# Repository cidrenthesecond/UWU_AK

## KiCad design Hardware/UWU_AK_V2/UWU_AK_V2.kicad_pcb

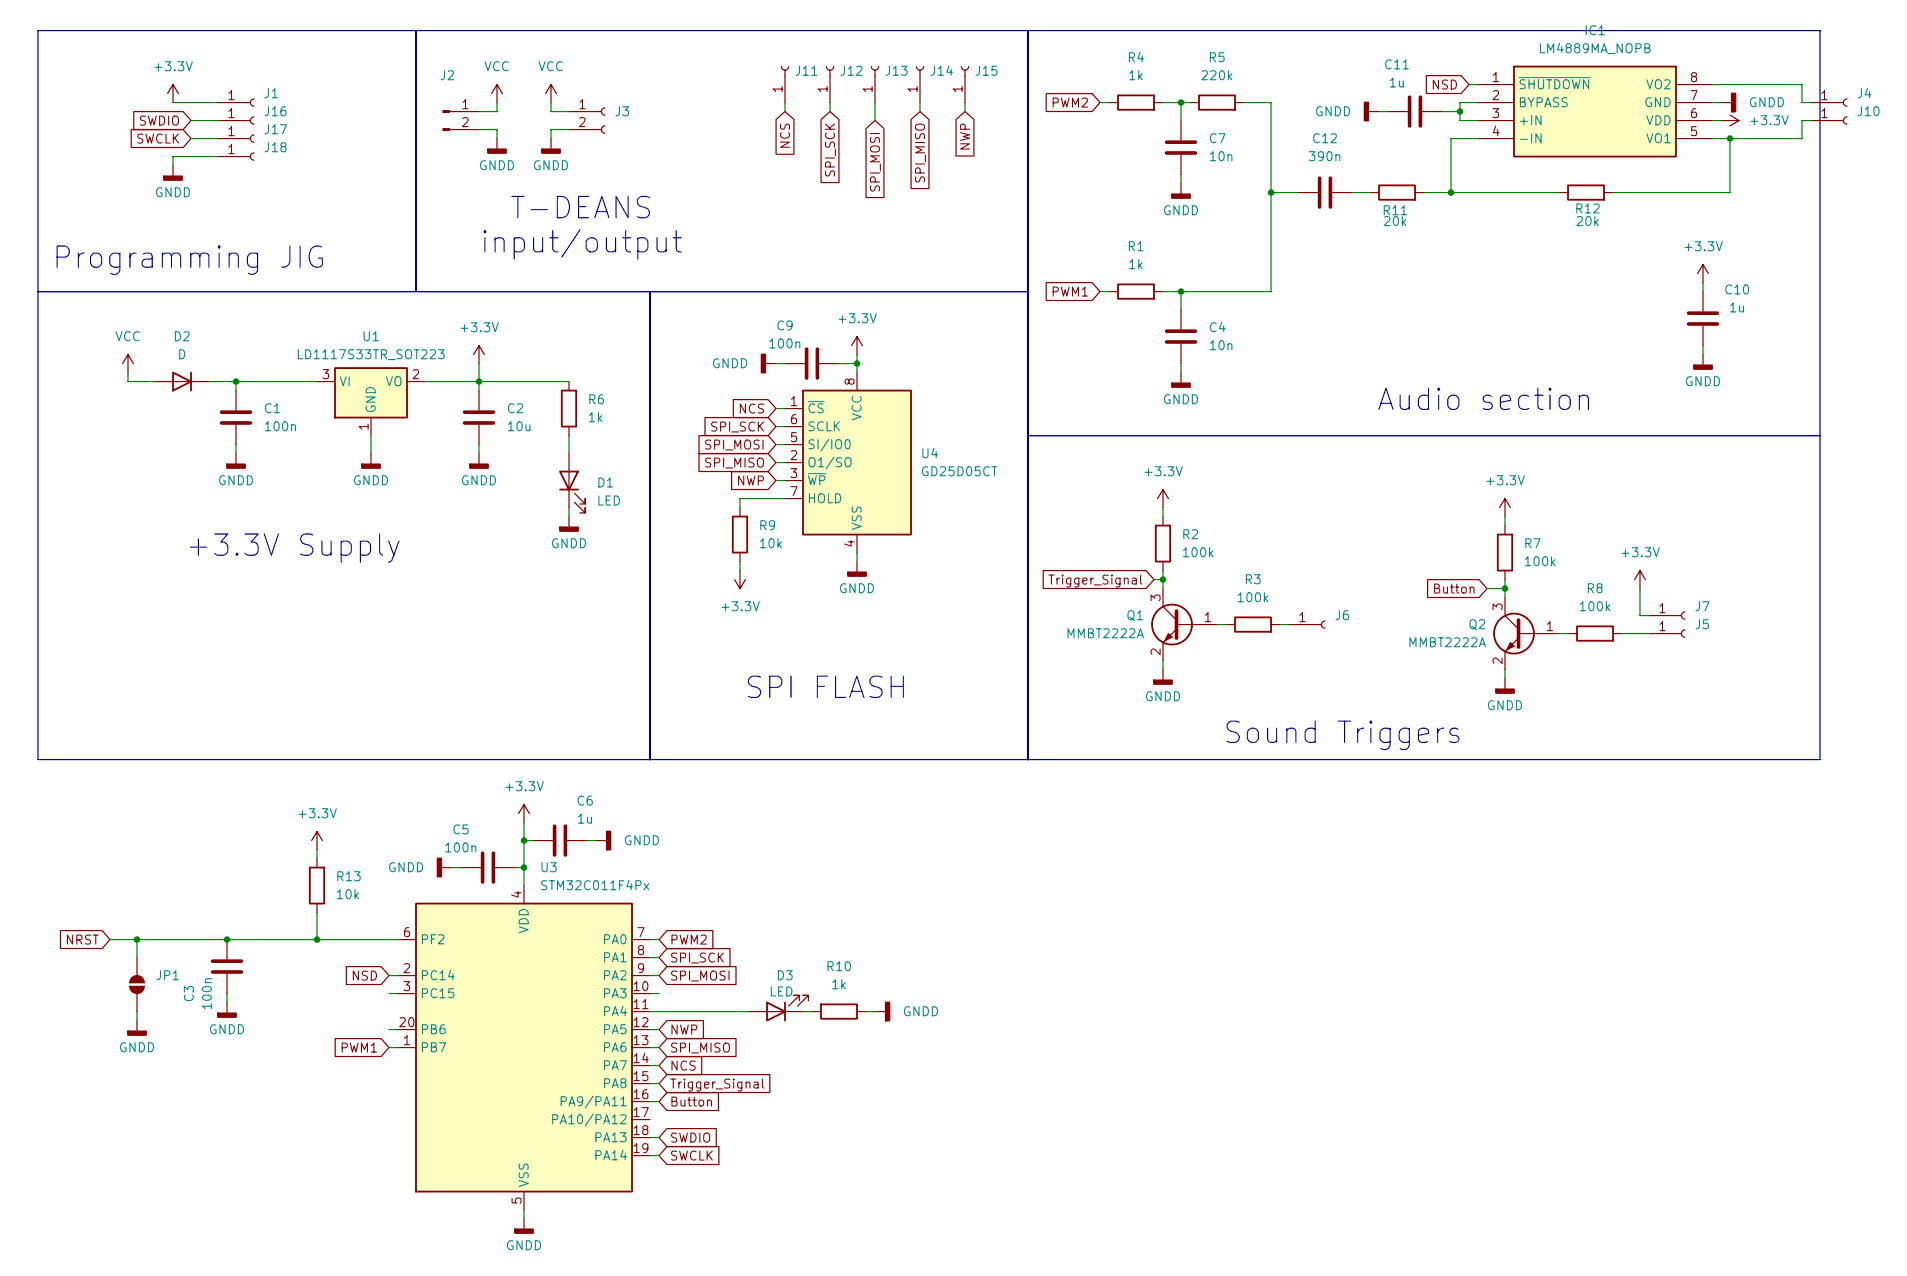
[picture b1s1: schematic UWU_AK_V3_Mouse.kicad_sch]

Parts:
C1, C3, C5, C9: 100n; C_0805_2012Metric_Pad1.18x1.45mm_HandSolder
C2: 10u; C_0805_2012Metric_Pad1.18x1.45mm_HandSolder
C4, C7: 10n; C_0805_2012Metric_Pad1.18x1.45mm_HandSolder
C6, C10, C11: 1u; C_0805_2012Metric_Pad1.18x1.45mm_HandSolder
C12: 390n; C_0805_2012Metric_Pad1.18x1.45mm_HandSolder
D1, D3: LED; LED_0805_2012Metric_Pad1.15x1.40mm_HandSolder
D2: D; D_SMA
IC1: LM4889MA_NOPB; SOIC127P600X175-8N; Manufacturer_Part_Number LM4889MA/NOPB
J1, J4, J5, J6, J7, J10, J18: Conn_01x01_Socket; SolderWirePad_1x01_SMD_2x4mm
J2: Conn_01x02_Pin; T_DEANS_MALE_1
J3: Conn_01x02_Socket; T_DEANS_FEMALE_2
J11, J12, J13, J14, J15, J16, J17: Conn_01x01_Socket; SolderWirePad_1x01_SMD_1x2mm
JP1: SolderJumper_2_Open; SolderJumper-2_P1.3mm_Open_TrianglePad1.0x1.5mm
Q1, Q2: MMBT2222A; SOT-23
R1, R4, R6, R10: 1k; R_0805_2012Metric_Pad1.20x1.40mm_HandSolder
R2, R3, R7, R8: 100k; R_0805_2012Metric_Pad1.20x1.40mm_HandSolder
R5: 220k; R_0805_2012Metric_Pad1.20x1.40mm_HandSolder
R9, R13: 10k; R_0805_2012Metric_Pad1.20x1.40mm_HandSolder
R11, R12: 20k; R_0805_2012Metric_Pad1.20x1.40mm_HandSolder
U1: LD1117S33TR_SOT223; SOT-223-3_TabPin2
U3: STM32C011F4Px; TSSOP-20_4.4x6.5mm_P0.65mm
U4: GD25D05CT; JEITA_SOIC-8_3.9x4.9mm_P1.27mm

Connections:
+3.3V: C2.1, C5.2, C6.1, C9.2, C10.2, IC1.6 (VDD), J1.1, J7.1, R2.2, R6.2, R7.2, R9.1, R13.2, U1.2 (VO), U3.4 (VDD), U4.8 (VCC)
Button: Q2.3 (C), R7.1, U3.16 (PA9/PA11)
GNDD: C1.2, C2.2, C3.1, C4.2, C5.1, C6.2, C7.2, C9.1, C10.1, C11.1, D1.1 (K), IC1.7 (GND), J2.2, J3.2, J18.1, JP1.1 (A), Q1.2 (E), Q2.2 (E), R10.1, U1.1 (GND), U3.5 (VSS), U4.4 (VSS)
NCS: J11.1, U3.14 (PA7), U4.1 (~CS)
NRST: C3.2, JP1.2 (B), R13.1, U3.6 (PF2)
NSD: IC1.1 (~SHUTDOWN), U3.2 (PC14)
NWP: J15.1, U3.12 (PA5), U4.3 (~WP)
unnamed: C7.1, R4.2, R5.1
unnamed: C4.1, C12.1, R1.2, R5.2
unnamed: C12.2, R11.1
unnamed: D1.2 (A), R6.1
unnamed: C1.1, D2.1 (K), U1.3 (VI)
unnamed: D3.2 (A), U3.11 (PA4)
unnamed: D3.1 (K), R10.2
unnamed: C11.2, IC1.2 (BYPASS), IC1.3 (+IN)
unnamed: IC1.4 (-IN), R11.2, R12.1
unnamed: IC1.5 (VO1), J10.1, R12.2
unnamed: IC1.8 (VO2), J4.1
unnamed: J5.1, R8.2
unnamed: J6.1, R3.2
unnamed: Q1.1 (B), R3.1
unnamed: Q2.1 (B), R8.1
unnamed: R9.2, U4.7 (HOLD)
PWM1: R1.1, U3.1 (PB7)
PWM2: R4.1, U3.7 (PA0)
SPI_MISO: J14.1, U3.13 (PA6), U4.2 (O1/SO)
SPI_MOSI: J13.1, U3.9 (PA2), U4.5 (SI/IO0)
SPI_SCK: J12.1, U3.8 (PA1), U4.6 (SCLK)
SWCLK: J17.1, U3.19 (PA14)
SWDIO: J16.1, U3.18 (PA13)
Trigger_Signal: Q1.3 (C), R2.1, U3.15 (PA8)
VCC: D2.2 (A), J2.1, J3.1

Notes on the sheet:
SPI FLASH
Programming JIG
Audio section
+3.3V Supply
Sound Triggers
T-DEANS input/output

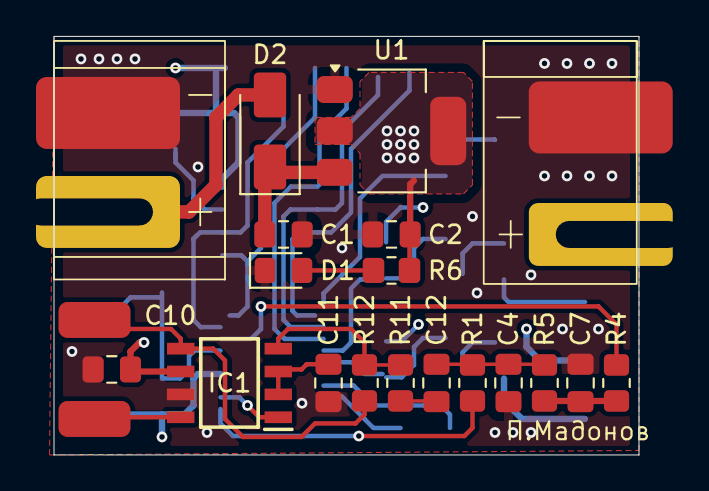
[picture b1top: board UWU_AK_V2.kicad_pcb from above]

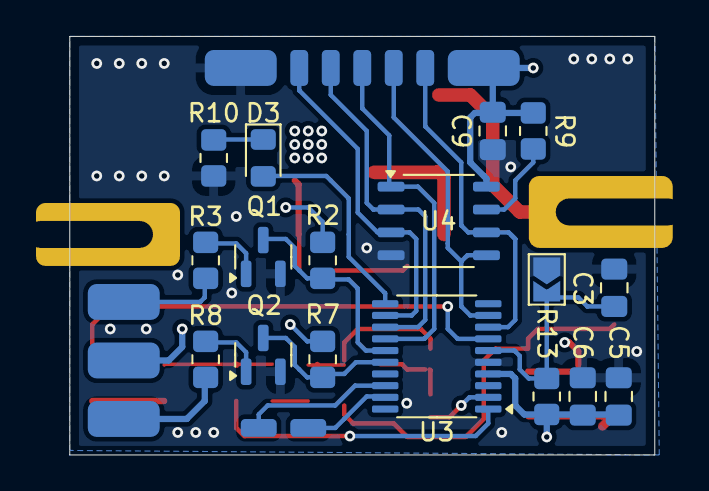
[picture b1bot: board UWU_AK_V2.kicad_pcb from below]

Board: 4 copper layers, 32.5 x 23.2 mm, 50 parts (29 on the bottom side), 32 nets.

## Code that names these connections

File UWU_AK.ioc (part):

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Mcu.Name=STM32C011F(4-6)Px
Mcu.Package=TSSOP20
Mcu.UserName=STM32C011F4Px
PA1.GPIOParameters=GPIO_Speed
PA1.GPIO_Speed=GPIO_SPEED_FREQ_VERY_HIGH
PA1.Mode=Full_Duplex_Master
PA1.Signal=SPI1_SCK
PA11\ [PA9].GPIOParameters=GPIO_Label,GPIO_ModeDefaultEXTI
PA11\ [PA9].GPIO_Label=Button
PA11\ [PA9].GPIO_ModeDefaultEXTI=GPIO_MODE_IT_FALLING
PA11\ [PA9].Signal=GPXTI11
PA13.Mode=Serial_Wire
PA13.Signal=DEBUG_SWDIO
PA14-BOOT0.Mode=Serial_Wire
PA14-BOOT0.Signal=DEBUG_SWCLK
PA2.GPIOParameters=GPIO_Speed
PA2.GPIO_Speed=GPIO_SPEED_FREQ_VERY_HIGH
PA2.Mode=Full_Duplex_Master
PA2.Signal=SPI1_MOSI
PA4.GPIOParameters=GPIO_Label
PA4.GPIO_Label=LED
PA4.Signal=GPIO_Output
PA5.GPIOParameters=GPIO_Label
PA5.GPIO_Label=NWP
PA5.Signal=GPIO_Output
PA6.GPIOParameters=GPIO_Speed
PA6.GPIO_Speed=GPIO_SPEED_FREQ_VERY_HIGH
PA6.Mode=Full_Duplex_Master
PA6.Signal=SPI1_MISO
PA7.GPIOParameters=GPIO_Label
PA7.GPIO_Label=NCS
PA7.Signal=GPIO_Output
PA8.GPIOParameters=GPIO_Label,GPIO_ModeDefaultEXTI
PA8.GPIO_Label=Trigger
PA8.GPIO_ModeDefaultEXTI=GPIO_MODE_IT_FALLING
PA8.Signal=GPXTI8
PB7.GPIOParameters=GPIO_Label
PB7.GPIO_Label=PWM1
PB7.Signal=S_TIM1_CH4
PC14-OSCX_IN\ (PC14).GPIOParameters=GPIO_Label
PC14-OSCX_IN\ (PC14).GPIO_Label=NSD
PC14-OSCX_IN\ (PC14).Signal=GPIO_Output
RCC.HSE_VALUE=8000000
RCC.SYSCLKFreq_VALUE=48000000
board=custom

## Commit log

2026-01-15 version1
2026-01-15 test pullrequest
2026-01-15 double buffer .c .h added
2026-01-16 systems works, click bugs out, cracks
2026-01-16 Click fixed, still cracks
2026-01-30 cracks are barely audible, minor fixes
2026-01-30 major readability improvements
2026-02-10 Addition of hardware files
